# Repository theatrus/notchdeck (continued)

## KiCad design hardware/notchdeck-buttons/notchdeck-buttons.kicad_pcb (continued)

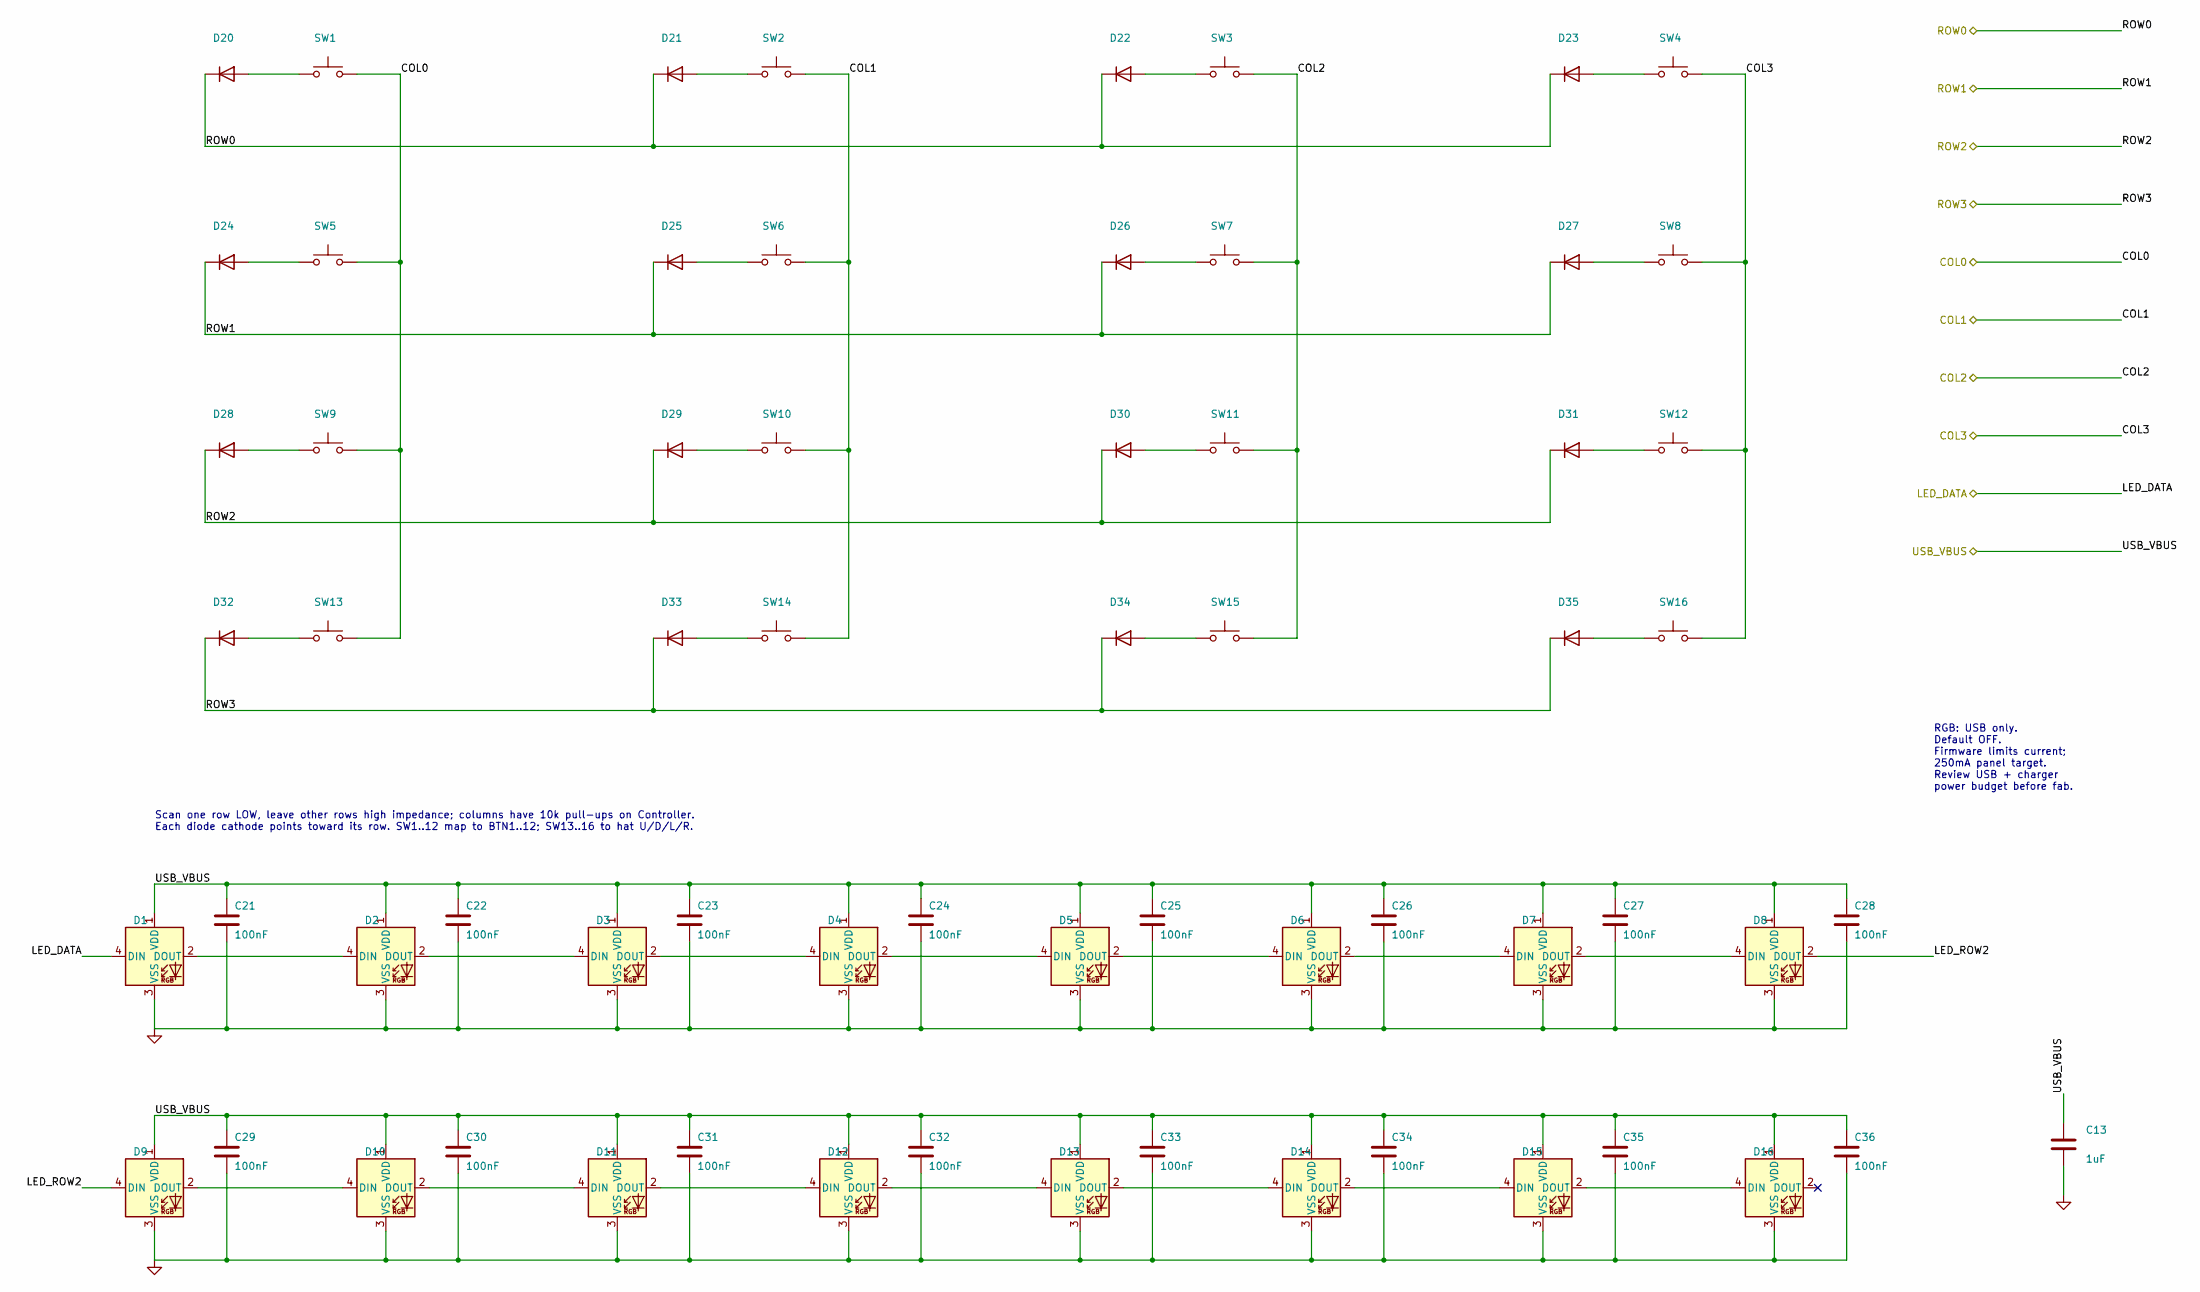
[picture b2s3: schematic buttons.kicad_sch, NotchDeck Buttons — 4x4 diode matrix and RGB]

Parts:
C13: 1uF; C_0805_2012Metric; MPN CL21B105KBFNNNE; LCSC C28323
C21, C22, C23, C24, C25, C26, C27, C28, C29, C30, C31, C32, C33, C34, C35, C36: 100nF; C_0402_1005Metric; MPN CL05B104KO5NNNC; LCSC C1525
D1, D2, D3, D4, D5, D6, D7, D8, D9, D10, D11, D12, D13, D14, D15, D16: WS2812B; LED_XINGLIGHT_XL-5050RGBC-2812B; MPN XL-5050RGBC-2812B; LCSC C2843785
D20, D21, D22, D23, D24, D25, D26, D27, D28, D29, D30, D31, D32, D33, D34, D35: 1N4148W; D_SOD-123; MPN 1N4148W; LCSC C81598
SW1, SW2, SW3, SW4, SW5, SW6, SW7, SW8, SW9, SW10, SW11, SW12, SW13, SW14, SW15, SW16: SW_Push; SW_Push_1P1T_XKB_TS-1187A; MPN TS-1187A-B-A-B; LCSC C318884

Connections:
/Buttons/LED_ROW2: D8.2 (DOUT), D9.4 (DIN)
/COL0: SW1.2, SW5.2, SW9.2, SW13.2; also elsewhere on the board
/COL1: SW2.2, SW6.2, SW10.2, SW14.2; also elsewhere on the board
/COL2: SW3.2, SW7.2, SW11.2, SW15.2; also elsewhere on the board
/COL3: SW4.2, SW8.2, SW12.2, SW16.2; also elsewhere on the board
/LED_DATA: D1.4 (DIN); also elsewhere on the board
/ROW0: D20.1 (K), D21.1 (K), D22.1 (K), D23.1 (K); also elsewhere on the board
/ROW1: D24.1 (K), D25.1 (K), D26.1 (K), D27.1 (K); also elsewhere on the board
/ROW2: D28.1 (K), D29.1 (K), D30.1 (K), D31.1 (K); also elsewhere on the board
/ROW3: D32.1 (K), D33.1 (K), D34.1 (K), D35.1 (K); also elsewhere on the board
unnamed: D1.2 (DOUT), D2.4 (DIN)
unnamed: D2.2 (DOUT), D3.4 (DIN)
unnamed: D3.2 (DOUT), D4.4 (DIN)
unnamed: D4.2 (DOUT), D5.4 (DIN)
unnamed: D5.2 (DOUT), D6.4 (DIN)
unnamed: D6.2 (DOUT), D7.4 (DIN)
unnamed: D7.2 (DOUT), D8.4 (DIN)
unnamed: D9.2 (DOUT), D10.4 (DIN)
unnamed: D10.2 (DOUT), D11.4 (DIN)
unnamed: D11.2 (DOUT), D12.4 (DIN)
unnamed: D12.2 (DOUT), D13.4 (DIN)
unnamed: D13.2 (DOUT), D14.4 (DIN)
unnamed: D14.2 (DOUT), D15.4 (DIN)
unnamed: D15.2 (DOUT), D16.4 (DIN)
unnamed: D20.2 (A), SW1.1
unnamed: D21.2 (A), SW2.1
unnamed: D22.2 (A), SW3.1
unnamed: D23.2 (A), SW4.1
unnamed: D24.2 (A), SW5.1
unnamed: D25.2 (A), SW6.1
unnamed: D26.2 (A), SW7.1
unnamed: D27.2 (A), SW8.1
unnamed: D28.2 (A), SW9.1
unnamed: D29.2 (A), SW10.1
unnamed: D30.2 (A), SW11.1
unnamed: D31.2 (A), SW12.1
unnamed: D32.2 (A), SW13.1
unnamed: D33.2 (A), SW14.1
unnamed: D34.2 (A), SW15.1
unnamed: D35.2 (A), SW16.1

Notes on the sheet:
Scan one row LOW, leave other rows high impedance; columns have 10k pull-ups on Controller. Each diode cathode points toward its row. SW1..12 map to BTN1..12; SW13..16 to hat U/D/L/R.
RGB: USB only. Default OFF. Firmware limits current; 250mA panel target. Review USB + charger power budget before fab.

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
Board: 2 copper layers, 89 parts (0 on the bottom side), 52 nets, no tracks yet.

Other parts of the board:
H1, H2, H3, H4: M3 provisional; MountingHole_3.2mm_M3

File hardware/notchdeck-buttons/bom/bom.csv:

Reference,Qty,Value,Footprint,MPN,Manufacturer,LCSC,LC_Stock,Chosen_Distributor,Datasheet,Validated,DNP,Notes
"C1,C3,C4,C5,C20,C21,C22,C23,C24,C25,C26,C27,C28,C29,C30,C31,C32,C33,C34,C35,C36",21,100nF,0402,CL05B104KO5NNNC,Samsung Electro-Mechanics,C1525,,LCSC,https://datasheet.lcsc.com/datasheet/pdf/02336ea48ea44ca18c7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,Yes,,100nF 16V X7R ±10% 0402 Multilayer Ceramic Capacitors MLCC - SMD/SMT ROHS
C2,1,4.7uF,0805,CL21A475KAQNNNE,Samsung Electro-Mechanics,C1779,,LCSC,https://datasheet.lcsc.com/datasheet/pdf/02336ea48ea44ca18c7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,Yes,,25V 4.7uF X5R ±10% 0805 Multilayer Ceramic Capacitors MLCC - SMD/SMT ROHS
C13,1,1uF,0805,CL21B105KBFNNNE,Samsung Electro-Mechanics,C28323,,LCSC,https://datasheet.lcsc.com/datasheet/pdf/02336ea48ea44ca18c7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,Yes,,1uF 50V X7R ±10% 0805 Multilayer Ceramic Capacitors MLCC - SMD/SMT ROHS
"D1,D2,D3,D4,D5,D6,D7,D8,D9,D10,D11,D12,D13,D14,D15,D16",16,WS2812B,SMD5050-4P,XL-5050RGBC-2812B,XINGLIGHT,C2843785,,LCSC,https://datasheet.lcsc.com/datasheet/pdf/40b65f6fea0587c0483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,Yes,,Same RGB part for D1-D16. Check pin 1 and polarity in CPL preview; firmware brightness/current limit required.
"D20,D21,D22,D23,D24,D25,D26,D27,D28,D29,D30,D31,D32,D33,D34,D35",16,1N4148W,SOD-123,1N4148W,ST(Semtech),C81598,,LCSC,https://datasheet.lcsc.com/datasheet/pdf/8abd7fc00ebe41ffb03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,Yes,,"Matrix isolation: cathode (pad1) to row; anode to switch, then column. Scan one row low, others high impedance."
J1,1,TO MAIN J15 / FFC,"SMD,P=1mm,卧贴",AFA07-S06FCA-00,JUSHUO,C262712,,LCSC,https://datasheet.lcsc.com/datasheet/pdf/b01391708457137d9b8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,Yes,,6-way 1mm bottom-contact FFC. Molex 0151670213 Type A cable: main J15 pin n -> button J1 pin 7-n. Cable bought once per set from DigiKey; power off to insert.
"R1,R2,R3,R4,R5",5,10k,0402,0402WGF1002TCE,UNI-ROYAL,C25744,,LCSC,https://datasheet.lcsc.com/datasheet/pdf/0a975aaa49b7c97f38a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,Yes,,-55℃~+155℃ 10kΩ 50V 62.5mW Thick Film Resistor ±1% ±100ppm/℃ 0402 Chip Resistor - Surface Mount ROHS
"R6,R7,R26",3,100k,0402,0402WGF1003TCE,UNI-ROYAL,C25741,,LCSC,https://datasheet.lcsc.com/datasheet/pdf/0a975aaa49b7c97f38a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,Yes,,-55℃~+155℃ 100kΩ 50V 62.5mW Thick Film Resistor ±1% ±100ppm/℃ 0402 Chip Resistor - Surface Mount ROHS
R11,1,330,0402,0402WGF3300TCE,UNI-ROYAL,C25104,,LCSC,https://datasheet.lcsc.com/datasheet/pdf/0a975aaa49b7c97f38a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,Yes,,-55℃~+155℃ 330Ω 50V 62.5mW Thick Film Resistor ±1% ±100ppm/℃ 0402 Chip Resistor - Surface Mount ROHS
"SW1,SW2,SW3,SW4,SW5,SW6,SW7,SW8,SW9,SW10,SW11,SW12,SW13,SW14,SW15,SW16",16,SW_Push,"SMD-4P,5.1x5.1mm",TS-1187A-B-A-B,XKB Connection,C318884,,LCSC,https://datasheet.lcsc.com/datasheet/pdf/56c8799ae5193945a16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,Yes,,
U1,1,STM32G030F6P6TR,TSSOP-20,STM32G030F6P6TR,ST,C529330,,LCSC,https://datasheet.lcsc.com/datasheet/pdf/753f35401d4598e355b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,Yes,,Use owned JLCPCB private stock for five button boards. I2C target 0x20; requires separate button-board firmware and SWD programming.
U2,1,USBLC6-2SC6,SOT-23-6L,USBLC6-2SC6,ST,C7519,,LCSC,https://datasheet.lcsc.com/datasheet/pdf/0d3a2ab954b34651a06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,Yes,,
U8,1,74AHCT1G125,SOT-23-5,SN74AHCT1G125DBVR,TI,C7484,,LCSC,https://datasheet.lcsc.com/datasheet/pdf/74b1f7dfbe12452e8a3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,Yes,,AHCT with TTL-compatible input at 5 V required; do not substitute AHC/HC.

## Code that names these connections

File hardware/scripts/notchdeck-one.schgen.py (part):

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p = s.pin("SW17", 1)
q = s.pin("C6", 1)
s.wire(p, (q[0], p[1]), q)
s.label("nRESET", (q[0], p[1]))
s.stub("SW17", 2, "GND", kind="power")
s.stub("C6", 2, "GND", kind="power")
for i, n in enumerate(PWR_PORTS + LEVER_PORTS + CTRL_PORTS + ACT_PORTS):
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s.note(
    10,
    88,
    "SWD headers are parallel; VTref is 3V3. SWO is unused.\nReset: P0.18 / UICR reset enabled; also resets handle mux.\nRev G: P0.20 SOL1, P0.13 SOL2, P0.22 BUZZ; active high.\n9 spare GPIOs; calibrated RC LFCLK, no LFXO/NFC.\nActuator firmware must default OFF; see ACTUATORS.md.",
)
s.finish()

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s.place("J1", 16, 24, ref_offset=(-10.16, -27.94), value_offset=(-10.16, -25.4))
s.place("U7", 53, 23, ref_offset=(-5.08, -12.7), value_offset=(-5.08, -10.16))
for pin in ["A4", "A9", "B4", "B9"]:
    s.stub("J1", pin, "USB_VBUS")
for pin in ["A1", "A12", "B1", "B12", "SH"]:
    s.stub("J1", pin, "GND", kind="power")
s.nc("J1", "A8", "B8")
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d = s.pin("D19", 1)
q = s.pin("Q1", 2)
s.wire(d, (96 * G, d[1]), (96 * G, q[1]), q)
s.label("VSYS", (96 * G, q[1]))
s.power("VSYS", (96 * G, q[1]), flag=True)
s.place("R5", 80, 38, 90, ref_offset=(-2.54, -5.08), value_offset=(-2.54, -2.54))
s.place("R4", 92, 44)
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c = s.pin("C7", 1)
s.wire(a, (c[0], a[1]), c)
s.wire(b, (121 * G, b[1]), (121 * G, a[1]))
s.label("VSYS", (c[0], a[1]))
a = s.pin("U2", 5)
for r in ["C8", "C9"]:
    p = s.pin(r, 1)
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s.place("R59",14,77)
s.stub("R59",1,"+3V3",kind="power")
a,b=s.pin("R59",2),s.pin("Q6",1)
s.wire(a,(a[0],b[1]),b);s.label("CHARGE_ENABLE",(a[0],b[1]))
s.port("CHARGE_ENABLE", 80, 102)
s.stub("U3", 2, "GND", kind="power")
s.place("C18", 20, 57)
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a = s.pin("U3", 3)
b = s.pin("C19", 1)
s.wire(a, (b[0], a[1]), b)
s.label("BAT_PROT", a)
s.stub("C19", 2, "GND", kind="power")
s.stub("U3", 1, "CHG_STAT")
s.place("R22", 53, 81)
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s.stub("C10", 2, "GND", kind="power")
for pin in [1, 4, 6, 9]:
    s.stub("U4", pin, "GND", kind="power")
for pin, net in [(5, "FG_ALRT"), (7, "I2C1_SCL"), (8, "I2C1_SDA")]:
    s.stub("U4", pin, net)
for r, net, x in [("R6", "I2C1_SDA", 134), ("R7", "I2C1_SCL", 143), ("R8", "FG_ALRT", 152)]:
    s.place(r, x, 63)
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
s = Capture(LEVER)
s.place("U9", 28, 23, ref_offset=(7.62, -22.86), value_offset=(7.62, -20.32))
for pin, net in {13: "I2C0_SDA", 12: "I2C0_SCL", 3: "nRESET",
                 5: "POWER_MAG_SDA", 6: "POWER_MAG_SCL",
                 9: "BRAKE_MAG_SDA", 10: "BRAKE_MAG_SCL",
                 4: "MUX_INT0", 8: "MUX_INT1"}.items():
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for pin in (4, 8):
    s.stub("U5", pin, "GND", kind="power")
s.nc("U5", 3, 5)
for pin, ref, net, y in [(6, "R37", "POWER_MAG_SDA", 23), (7, "R38", "POWER_MAG_SCL", 28)]:
    s.place(ref, 132, y, 90, ref_offset=(-2.54, -5.08), value_offset=(-2.54, -2.54))
    p, q = s.pin("U5", pin), s.pin(ref, 1)
    s.wire(p, (118 * G, p[1]), (118 * G, q[1]), q)
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s = Capture(CONTROLS)
# Rev E intelligent button board: 0x20 on I2C0 upstream of the handle mux.
s.place("J15",18,22,180,ref_offset=(-2.54,-12.7),value_offset=(-2.54,-10.16))
for pin,net in {1:"GND",2:"+3V3",3:"I2C0_SDA",4:"I2C0_SCL",5:"PANEL_INT",6:"USB_VBUS"}.items():
    s.stub("J15",pin,net)
s.place("U12",47,24,ref_offset=(7.62,-12.7),value_offset=(7.62,-10.16))
for pin,net in {1:"I2C0_SDA",6:"I2C0_SDA",3:"I2C0_SCL",4:"I2C0_SCL",5:"+3V3",2:"GND"}.items():
    s.stub("U12",pin,net,kind="power" if net in ("+3V3","GND") else "label")
s.place("R42",77,20);s.stub("R42",1,"+3V3",kind="power");s.stub("R42",2,"PANEL_INT")
s.place("C44",91,20);s.stub("C44",1,"+3V3",kind="power");s.stub("C44",2,"GND",kind="power")
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a = s.pin("R25", 2)
b = s.pin("C37", 1)
s.wire(a, (b[0], a[1]), b)
s.label("REVERSER_AIN", (b[0], a[1]))
s.stub("C37", 2, "GND", kind="power")
s.port("REVERSER_AIN", 126, 43)
s.note(122, 48, "J9: 1=3V3, 2=common, 3=GND.\nSPDT center-off: F / N / R.")
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for ref in ("C45","C46","D23"):
    b=s.pin(ref,1);s.wire(a,(b[0],a[1]),b)
    s.stub(ref,2,"GND",kind="power")
s.label("BAT_PROT",(83*G,a[1]))
s.port("BAT_PROT",73,11)
# Reverse-only bootstrap path permits charging a depleted/disabled pack.
# K=raw battery, A=charger/protected rail. It cannot bypass discharge protection.
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s.stub("R52",1,"BAT_RAW")
a,b=s.pin("R52",2),s.pin("R53",1);s.wire(a,b)
p=s.pin("U13",1);s.wire(a,(40*G,a[1]),(40*G,p[1]),p)
s.label("BAT_ENABLE",(30*G,a[1]));s.stub("R53",2,"GND",kind="power")
s.place("Q5",121,23,ref_offset=(5.08,0),value_offset=(5.08,2.54))
s.place("R54",108,23,90,ref_offset=(-2.54,-5.08),value_offset=(-2.54,-2.54))
s.place("R55",114,30)
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    drain, neg = s.pin(q, 2), s.pin(j, 2)
    a = s.pin(d, 2)
    s.wire(drain, a, (neg[0], a[1]), neg)
    s.label(["SOL1_LOW", "SOL2_LOW", "BUZZ_LOW"][i], (neg[0], a[1]))
    s.rail("BAT_PROT", [(j, 1), (d, 1)], 40)
    s.join((rg, 2), (q, 1))
    a, b = s.pin(pd, 1), s.pin(q, 1)
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            wiring += K.w_wire(100 * G, yy, 108 * G, yy) + K.w_label(n, 100 * G, yy, 180)
    if sh in (POWER, ACTUATORS):
        yy = (y + 3 + len(ports) * 2) * G
        pins.append(("BAT_PROT", "passive", 108 * G, yy, 180))
        wiring += K.w_wire(100 * G, yy, 108 * G, yy) + K.w_label("BAT_PROT", 100 * G, yy, 180)
    if sh in (POWER, ACTUATORS):
        yy = (y + 3 + (len(ports) + 1) * 2) * G
        pins.append(("CHARGE_ENABLE", "passive", 108 * G, yy, 180))
        wiring += K.w_wire(100 * G, yy, 108 * G, yy) + K.w_label("CHARGE_ENABLE", 100 * G, yy, 180)
    blocks += K.w_sheet(sh["name"], sh["file"], sh["uuid"], 108 * G, y * G, 41 * G, h * G, pins,
                        project="notchdeck-one", parent_path=f"/{ROOT_UUID}", page=sh["page"])
    pro.append([sh["uuid"], sh["name"]])
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
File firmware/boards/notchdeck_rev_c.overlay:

/* Rev C/D E73 module mapping. Apply as DTC_OVERLAY_FILE, replacing the DK overlay.
 * Board platform remains DK for SDK bring-up; bootloader/USB IDs still provisional. */
#include <zephyr/dt-bindings/gpio/gpio.h>
#include <zephyr/dt-bindings/pinctrl/nrf-pinctrl.h>
#include <zephyr/dt-bindings/i2c/i2c.h>

&pinctrl {
    notchdeck_i2c0_default: notchdeck_i2c0_default {
        group1 { psels = <NRF_PSEL(TWIM_SDA, 0, 26)>, <NRF_PSEL(TWIM_SCL, 0, 6)>; };
    };
    notchdeck_i2c0_sleep: notchdeck_i2c0_sleep {
        group1 { psels = <NRF_PSEL(TWIM_SDA, 0, 26)>, <NRF_PSEL(TWIM_SCL, 0, 6)>; low-power-enable; };
    };
    notchdeck_i2c1_default: notchdeck_i2c1_default {
        group1 { psels = <NRF_PSEL(TWIM_SDA, 0, 12)>, <NRF_PSEL(TWIM_SCL, 0, 7)>; };
    };
    notchdeck_i2c1_sleep: notchdeck_i2c1_sleep {
        group1 { psels = <NRF_PSEL(TWIM_SDA, 0, 12)>, <NRF_PSEL(TWIM_SCL, 0, 7)>; low-power-enable; };
    };
};
&i2c0 {
    compatible = "nordic,nrf-twim";
    status = "okay";
    clock-frequency = <I2C_BITRATE_STANDARD>;
    pinctrl-0 = <&notchdeck_i2c0_default>;
    pinctrl-1 = <&notchdeck_i2c0_sleep>;
    pinctrl-names = "default", "sleep";
};
&i2c1 {
    compatible = "nordic,nrf-twim";
    status = "okay";
    clock-frequency = <I2C_BITRATE_STANDARD>;
    pinctrl-0 = <&notchdeck_i2c1_default>;
    pinctrl-1 = <&notchdeck_i2c1_sleep>;
    pinctrl-names = "default", "sleep";
};
/* TWIM1 and SPIM1 share hardware: reserve instance 1 for the fuel gauge.
 * Future RGB SPI pinctrl must use instance 2/3. Disable DK UART pin conflicts. */
&spi0 { status = "disabled"; };
&spi1 { status = "disabled"; };
&uart0 { status = "disabled"; };
&uart1 { status = "disabled"; };
&spi3 { status = "disabled"; };
&pwm0 { status = "disabled"; };
&qspi { status = "disabled"; };
&nfct { status = "disabled"; };
&uicr { gpio-as-nreset; nfct-pins-as-gpios; };
&gpio0 {
    gpio-reserved-ranges = <18 1>;
    /delete-property/ gpio-line-names;
};
&gpio1 { /delete-property/ gpio-line-names; };
/ {
    /delete-node/ buttons;
    /delete-node/ leds;
    /delete-node/ pwmleds;
    aliases {
        /delete-property/ led0;
        /delete-property/ led1;
        /delete-property/ led2;
        /delete-property/ led3;
        /delete-property/ pwm-led0;
        /delete-property/ sw0;
        /delete-property/ sw1;
        /delete-property/ sw2;
        /delete-property/ sw3;
        /delete-property/ mcuboot-button0;
        /delete-property/ mcuboot-led0;
    };
    buttons: buttons {
        compatible = "gpio-keys";
        btn1 { gpios = <&gpio1 11 (GPIO_ACTIVE_LOW | GPIO_PULL_UP)>; };
        btn2 { gpios = <&gpio1 10 (GPIO_ACTIVE_LOW | GPIO_PULL_UP)>; };
        btn3 { gpios = <&gpio1 13 (GPIO_ACTIVE_LOW | GPIO_PULL_UP)>; };
        btn4 { gpios = <&gpio1 9 (GPIO_ACTIVE_LOW | GPIO_PULL_UP)>; };
        btn5 { gpios = <&gpio0 20 (GPIO_ACTIVE_LOW | GPIO_PULL_UP)>; };
        btn6 { gpios = <&gpio0 13 (GPIO_ACTIVE_LOW | GPIO_PULL_UP)>; };
        btn7 { gpios = <&gpio1 4 (GPIO_ACTIVE_LOW | GPIO_PULL_UP)>; };
        btn8 { gpios = <&gpio1 6 (GPIO_ACTIVE_LOW | GPIO_PULL_UP)>; };
        btn9 { gpios = <&gpio0 9 (GPIO_ACTIVE_LOW | GPIO_PULL_UP)>; };
        btn10 { gpios = <&gpio0 10 (GPIO_ACTIVE_LOW | GPIO_PULL_UP)>; };
        btn11 { gpios = <&gpio0 0 (GPIO_ACTIVE_LOW | GPIO_PULL_UP)>; };
        btn12 { gpios = <&gpio0 1 (GPIO_ACTIVE_LOW | GPIO_PULL_UP)>; };
    };
    handle_inputs {
        compatible = "gpio-keys";
        brake_s0: brake_s0 { gpios = <&gpio0 3 GPIO_ACTIVE_HIGH>; };
        brake_s1: brake_s1 { gpios = <&gpio0 28 GPIO_ACTIVE_HIGH>; };
        brake_s2: brake_s2 { gpios = <&gpio0 4 GPIO_ACTIVE_HIGH>; };
        brake_s3: brake_s3 { gpios = <&gpio0 5 GPIO_ACTIVE_HIGH>; };
        power_s0: power_s0 { gpios = <&gpio0 29 GPIO_ACTIVE_HIGH>; };
        power_s1: power_s1 { gpios = <&gpio0 31 GPIO_ACTIVE_HIGH>; };
        power_s2: power_s2 { gpios = <&gpio0 30 GPIO_ACTIVE_HIGH>; };
    };
};

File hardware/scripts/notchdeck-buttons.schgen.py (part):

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s.nc('U1',2,16)
s.place('J1',18,17,180,ref_offset=(-2.54,-12.7),value_offset=(-2.54,-10.16))
# Type A same-side contacts + identical bottom-contact connectors reverse numbering.
for pin,net in {1:'USB_VBUS',2:'IRQ_N',3:'SCL',4:'SDA',5:'+3V3',6:'GND'}.items():s.stub('J1',pin,net)
s.place('U2',26,43,ref_offset=(7.62,-12.7),value_offset=(7.62,-10.16))
for pin,net in {1:'SDA',6:'SDA',3:'SCL',4:'SCL',5:'+3V3',2:'GND'}.items():s.stub('U2',pin,net)
for ref,x in [('C1',91),('C2',100),('C5',109)]:
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s.stub('R6',1,'USB_VBUS');s.stub('R7',2,'GND',kind='power')
s.place('C4',63,83)
s.wire((51*2.54,78*2.54),(63*2.54,78*2.54),s.pin('C4',1))
s.label('VBUS_SENSE',(55*2.54,78*2.54));s.stub('C4',2,'GND',kind='power')
s.place('U8',91,75,ref_offset=(15.24,-17.78),value_offset=(15.24,-15.24))
for pin,net in {1:'GND',3:'GND',5:'USB_VBUS',2:'RGB_PWM'}.items():s.stub('U8',pin,net)
s.place('R26',74,89);s.stub('R26',1,'RGB_PWM');s.stub('R26',2,'GND',kind='power')
s.place('R11',107,75,90,ref_offset=(-2.54,-5.08),value_offset=(-2.54,-2.54));s.join(('U8',4),('R11',1));s.stub('R11',2,'LED_DATA')
s.place('C20',119,79);s.stub('C20',1,'USB_VBUS');s.stub('C20',2,'GND',kind='power')
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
